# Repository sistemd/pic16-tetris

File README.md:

# PIC16 Tetris

This is an embedded Tetris clone written in C to run on a PIC16F884 device.
It uses four simple buttons and an LCD display,
in particular MikroE's https://www.mikroe.com/glcd-128x64, although
another LCD module could probably also be made to work.

All the schematic files and a PCB file are in the `scheme` directory.
They were made using KiCad.

### Demo video

https://www.youtube.com/watch?v=IU35cAhXwaM

### Schematic

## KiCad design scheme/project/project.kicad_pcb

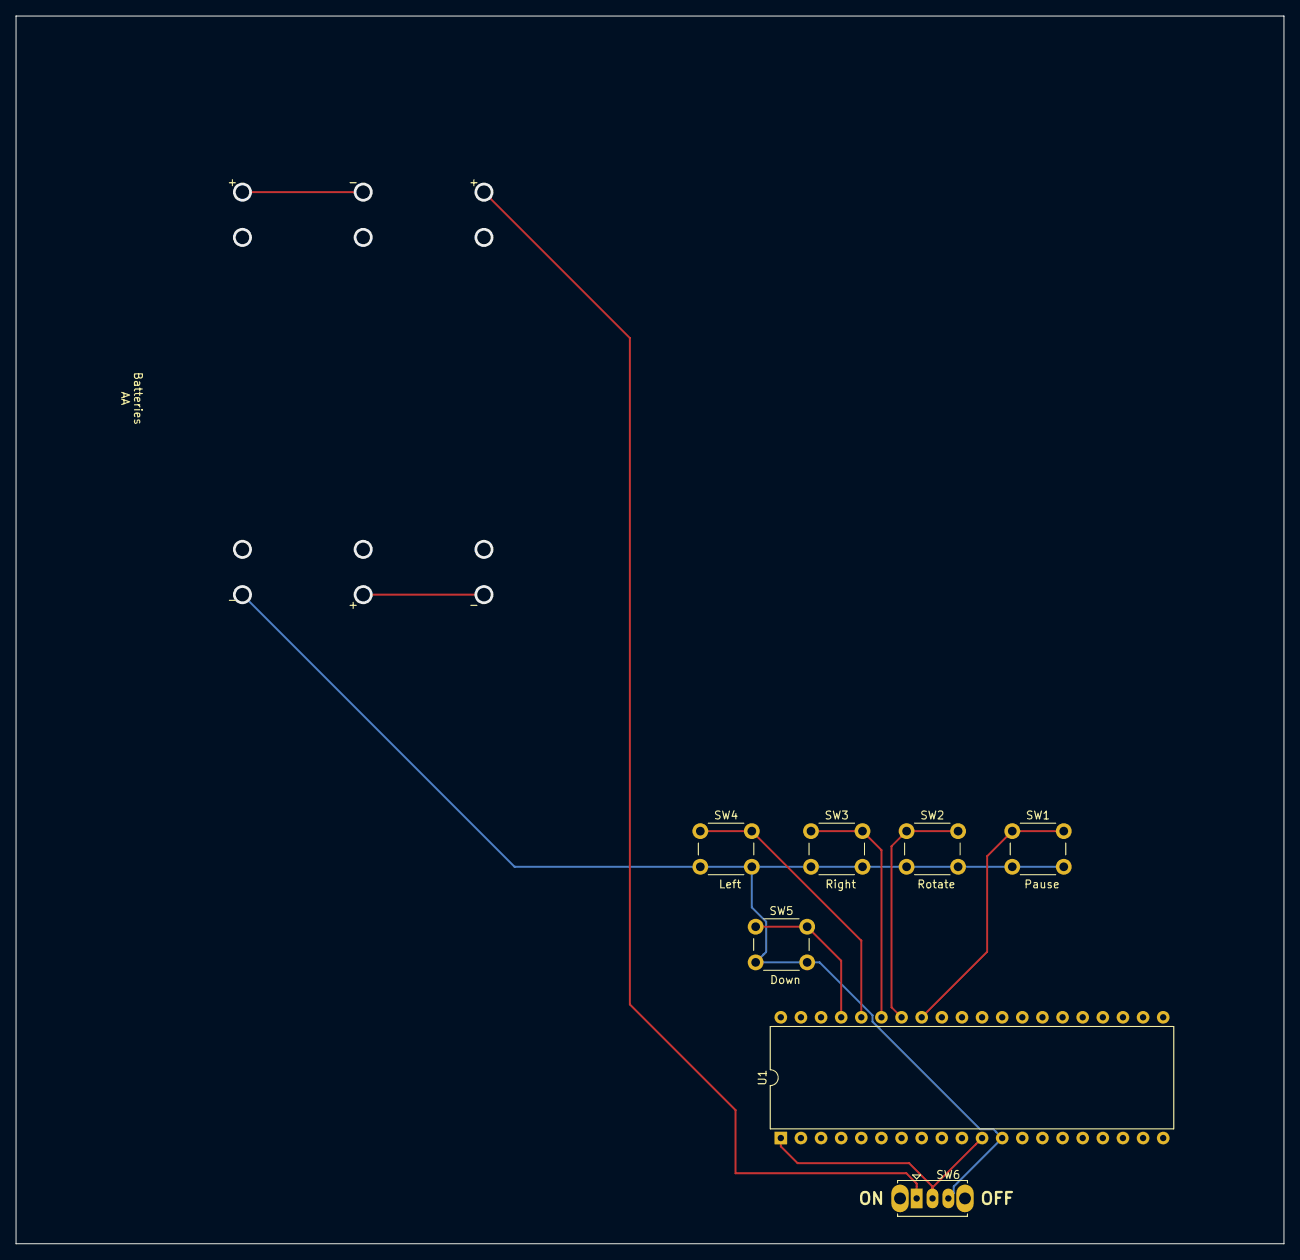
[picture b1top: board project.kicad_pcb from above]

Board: 2 copper layers, 160.0 x 154.9 mm, 7 parts (0 on the bottom side), 7 nets.

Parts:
SW1: Pause; SW_PUSH_6mm
SW2: Rotate; SW_PUSH_6mm
SW3: Right; SW_PUSH_6mm
SW4: Left; SW_PUSH_6mm
SW5: Down; SW_PUSH_6mm
SW6: Power_sw; SW_Slide_1P2T_CK_OS102011MS2Q
U1: PIC16F884; DIP-40_W15.24mm

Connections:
GND: SW1.2, SW2.2, SW3.2, SW4.2, SW5.2, SW6.3, U1.12
unnamed: SW1.1, U1.33
unnamed: SW2.1, U1.34
unnamed: SW3.1, U1.35
unnamed: SW4.1, U1.36
unnamed: SW5.1, U1.37
unnamed: SW6.2, U1.1, U1.11

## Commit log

2019-04-26 Added moving down, movement tests, moving down is still untested
2019-04-27 Tetris code is finished
2019-04-29 Non-timed version running on embedded hardware
2019-04-29 Embedded hardware runs the game, with timing
2019-04-29 Fixed a randomness issue, added code for embedding the logo image into memory and drawing it
2019-04-30 Made the logo smaller, fixed a big with rotating a unit and made the rotation always go clockwise
2019-04-30 Finished everything, no memory left for logo
2019-05-01 Added a KiCad scheme
2019-05-01 Fixed a bug
2019-05-10 Added a PCB and fixed up the scheme
2019-07-14 Changed the structure a bit and added a REAME
2019-07-15 Added schematic image
